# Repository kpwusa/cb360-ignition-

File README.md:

# cb360-ignition-
ignition development for a honda cb360

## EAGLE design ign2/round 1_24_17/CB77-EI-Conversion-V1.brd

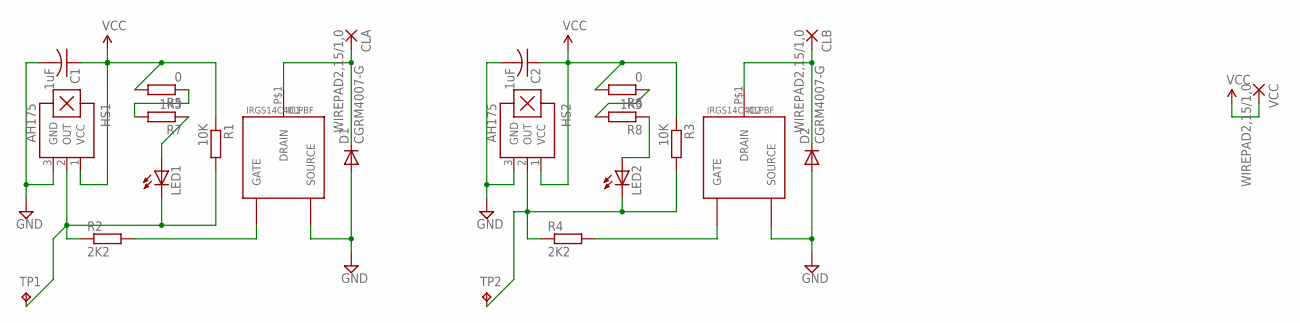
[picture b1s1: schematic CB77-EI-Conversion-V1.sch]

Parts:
C1, C2: .1uF; C0603K
CLA: WIREPAD2,15/1,0; 2,15/1,0
CLB: WIREPAD2,15/1,0; 2,15/1,0
D1, D2: CGRM4007-G; SOD-123_MINI-SMA
HS1, HS2: AH175; SOT23-W
IC1, IC2: IRGS14C40LPBF; TO-263AB
LED1, LED2: LED_E; LED_1206
R1, R3: 10K; R0805
R2, R4: 2K2; R0805
R5, R6: 0; R0805
R7, R8: 1K3; R0805
TP1, TP2: TPPAD1-17; P1-17
VCC: WIREPAD2,15/1,0; 2,15/1,0

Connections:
G1: IC1.P$2 (GATE), R2.2
G2: IC2.P$2 (GATE), R4.2
GND: C1.2, C2.2, D1.A, D2.A, HS1.3 (GND), HS2.3 (GND), IC1.P$3 (SOURCE), IC2.P$3 (SOURCE)
LHS: CLB.1, D2.C, IC2.P$1 (DRAIN)
unnamed: LED2.A, R8.1
unnamed: LED1.A, R7.1
unnamed: HS1.2 (OUT), LED1.C, R1.2, R2.1, TP1.TP
unnamed: R5.1, R7.2
unnamed: R6.1, R8.2
unnamed: HS2.2 (OUT), LED2.C, R3.2, R4.1, TP2.TP
RHS: CLA.1, D1.C, IC1.P$1 (DRAIN)
VCC: C1.1, C2.1, HS1.1 (VCC), HS2.1 (VCC), R1.1, R3.1, R5.2, R6.2, VCC.1

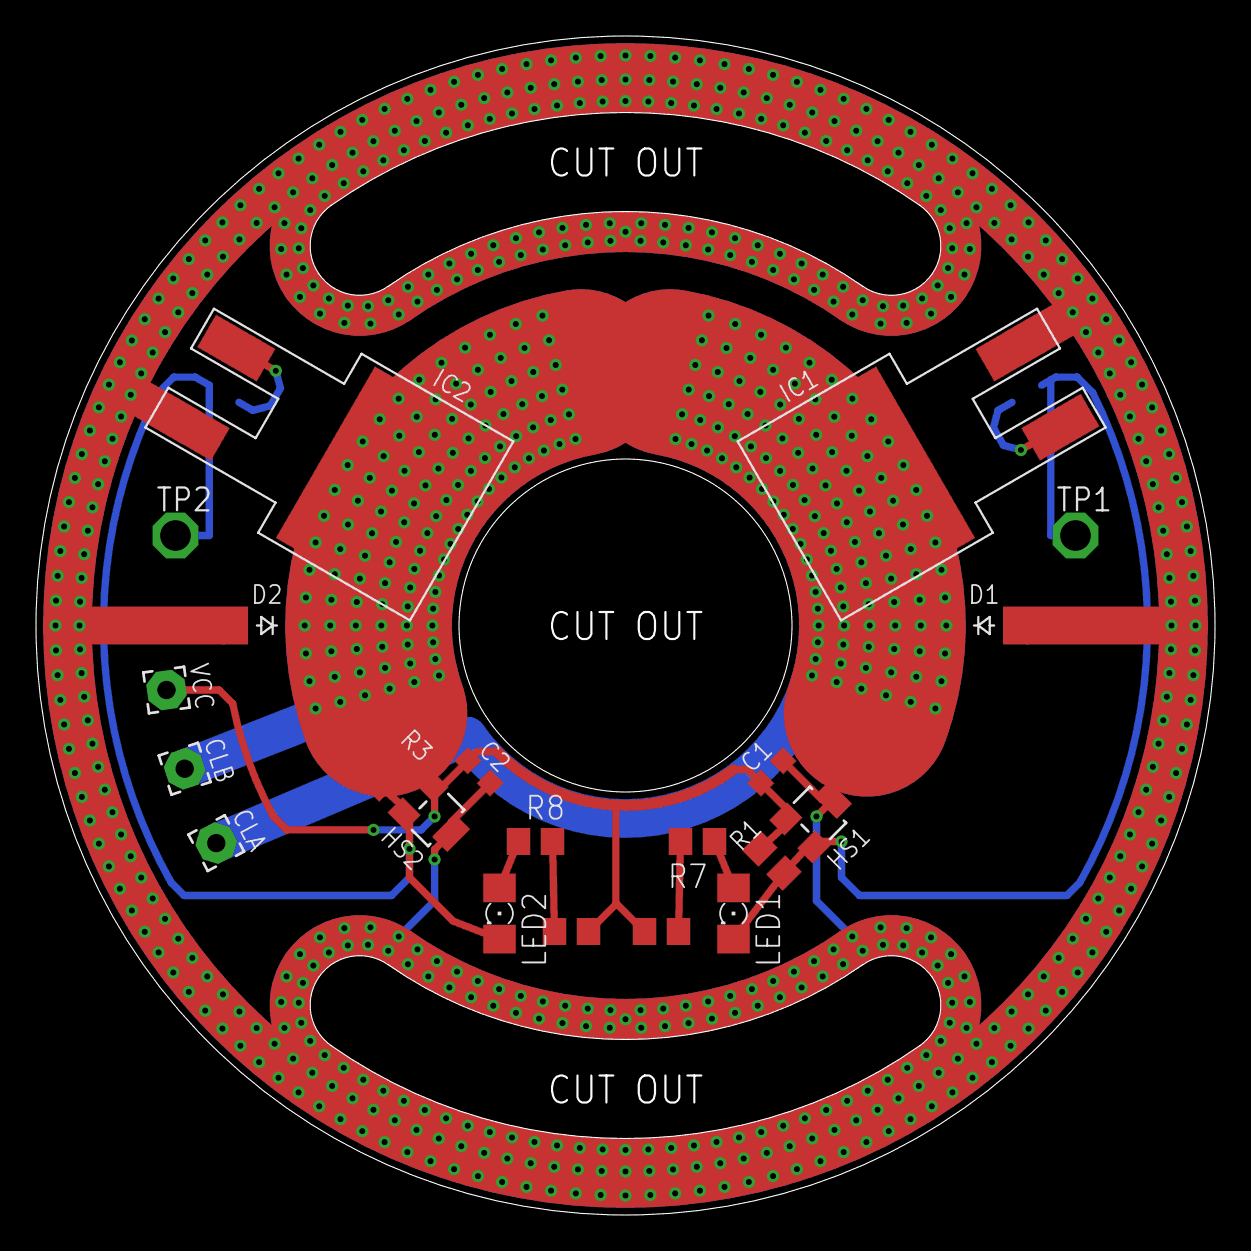
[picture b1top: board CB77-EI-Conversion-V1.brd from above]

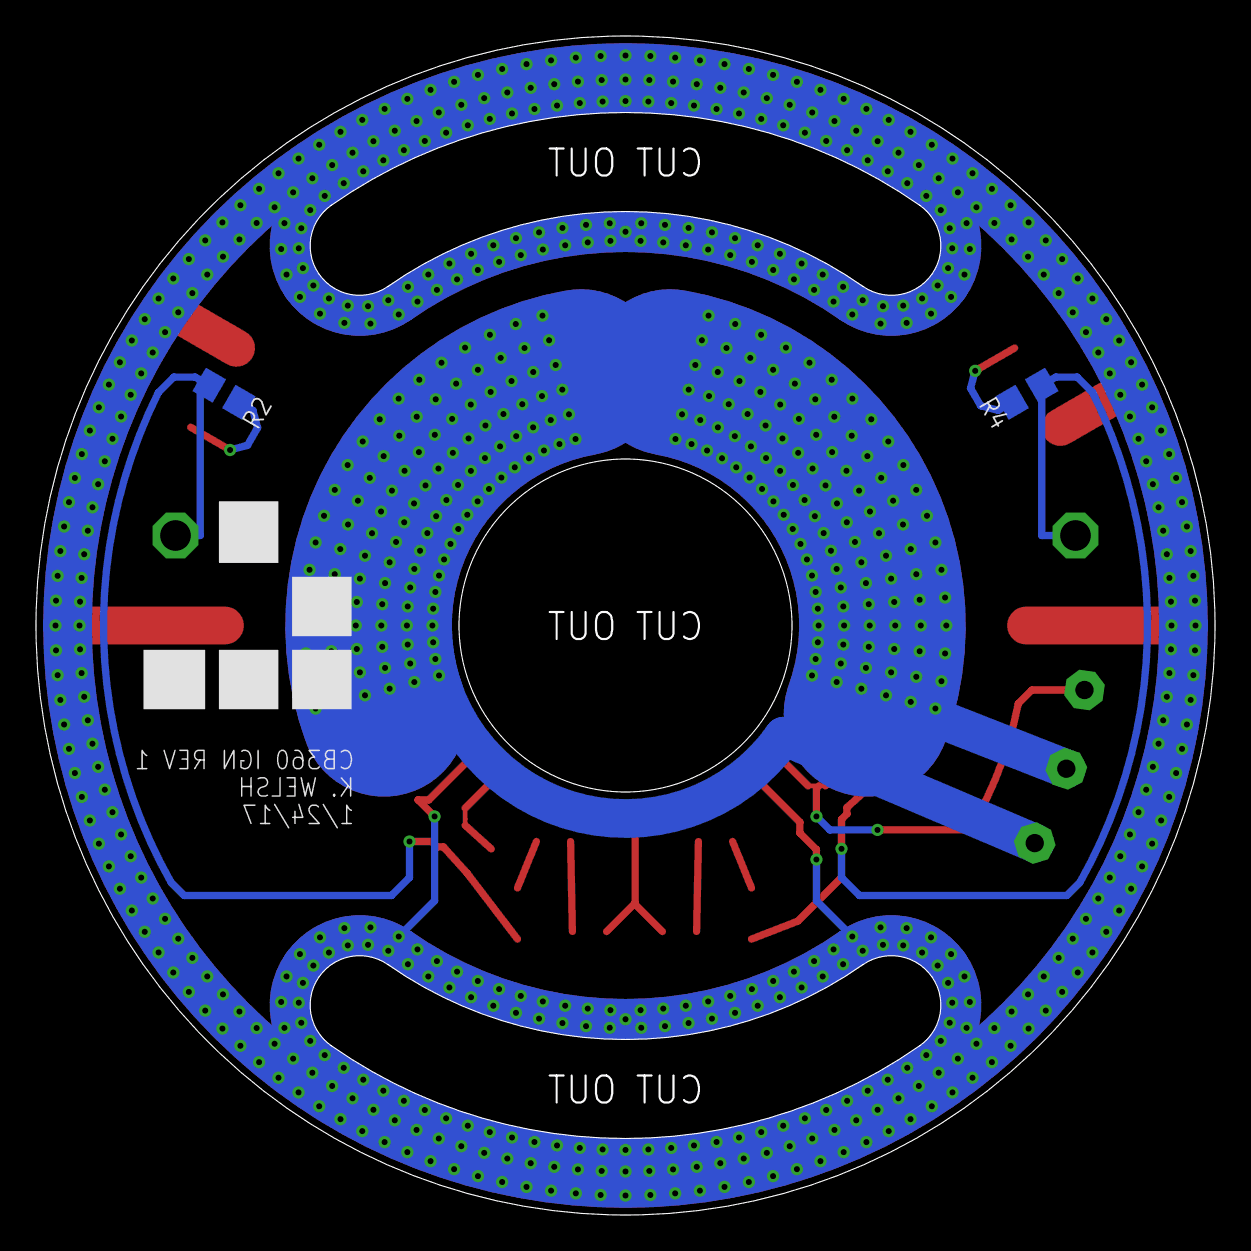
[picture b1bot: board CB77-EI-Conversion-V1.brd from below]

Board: 2 copper layers, 65.5 x 65.5 mm, 24 parts (3 on the bottom side), 12 nets.

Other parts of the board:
U$1: GLIDER3

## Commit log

2018-03-15 updated pcb and included mfg layout
    timing leds and breakout pads added to the ignition module.
    --fixed 90deg between cylinders
    --jumper pads added
    --optional pads for diodes and filter caps added.
    also included in the layout for mfg @ dirtypcb.com is the rev3 manicbug mesh node and assorted proto pcbs

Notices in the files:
parts and their libraries:
SparkFun-Aesthetics: Licensing: CC v3.0 Share-Alike You are welcome to use this library for commercial purposes.
